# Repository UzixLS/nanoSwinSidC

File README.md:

## nanoSwinSidC

SID emulator on ATmega.

This is custom PCB variant of SwinSID Nano project.

See https://www.c64-wiki.com/wiki/SwinSID and http://www.tolaemon.com/nss/

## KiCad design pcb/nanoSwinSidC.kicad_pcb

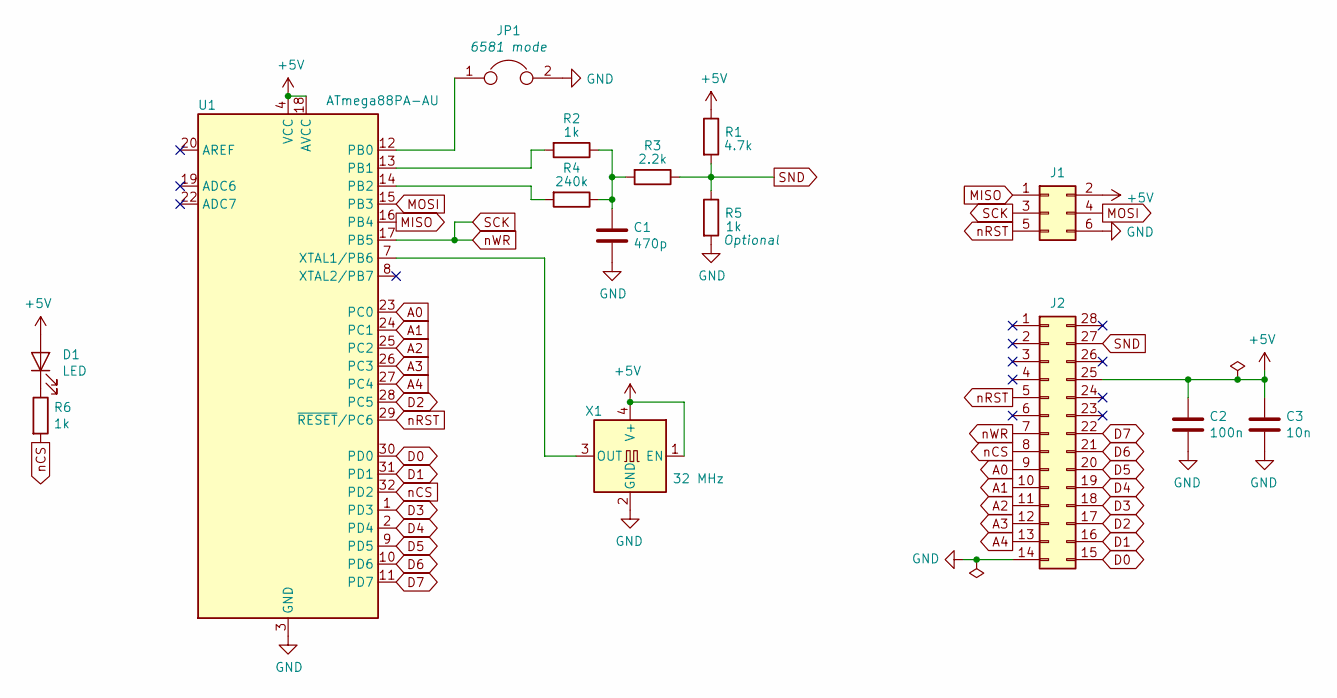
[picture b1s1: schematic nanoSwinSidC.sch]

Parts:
C1: 470p; C_0603_1608Metric_Pad1.05x0.95mm_HandSolder
C2: 100n; C_0603_1608Metric_Pad1.05x0.95mm_HandSolder
C3: 10n; C_0603_1608Metric_Pad1.05x0.95mm_HandSolder
D1: LED; LED_0805_2012Metric_Pad1.15x1.40mm_HandSolder
J1: Conn_02x03_Odd_Even; PinHeader_2x03_P2.54mm_Vertical
J2: Conn_02x14_Counter_Clockwise; DIP-28_W15.24mm
JP1: Jumper; PinHeader_1x02_P2.54mm_Horizontal
R1: 4.7k; R_0603_1608Metric_Pad1.05x0.95mm_HandSolder
R2, R5, R6: 1k; R_0603_1608Metric_Pad1.05x0.95mm_HandSolder
R3: 2.2k; R_0603_1608Metric_Pad1.05x0.95mm_HandSolder
R4: 240k; R_0603_1608Metric_Pad1.05x0.95mm_HandSolder
U1: ATmega88PA-AU; TQFP-32_7x7mm_P0.8mm
X1: 32 MHz; Oscillator_SMD_EuroQuartz_XO91-4Pin_7.0x5.0mm_HandSoldering

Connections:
+5V: C2.1, C3.1, D1.2 (A), J1.2, J2.25, R1.1, U1.4 (VCC), U1.6 (VCC), U1.18 (AVCC), X1.1 (EN), X1.4 (V+)
A0: J2.9, U1.23 (PC0)
A1: J2.10, U1.24 (PC1)
A2: J2.11, U1.25 (PC2)
A3: J2.12, U1.26 (PC3)
A4: J2.13, U1.27 (PC4)
D0: J2.15, U1.30 (PD0)
D1: J2.16, U1.31 (PD1)
D2: J2.17, U1.28 (PC5)
D3: J2.18, U1.1 (PD3)
D4: J2.19, U1.2 (PD4)
D5: J2.20, U1.9 (PD5)
D6: J2.21, U1.10 (PD6)
D7: J2.22, U1.11 (PD7)
GND: C1.2, C2.2, C3.2, J1.6, J2.14, JP1.2, R5.2, U1.3 (GND), U1.5 (GND), U1.21 (GND), X1.2 (GND)
MISO: J1.1, U1.16 (PB4)
MOSI: J1.4, U1.15 (PB3)
unnamed: C1.1, R2.1, R3.2, R4.1
unnamed: D1.1 (K), R6.1
unnamed: JP1.1, U1.12 (PB0)
unnamed: R2.2, U1.13 (PB1)
unnamed: R4.2, U1.14 (PB2)
unnamed: U1.7 (XTAL1/PB6), X1.3 (OUT)
SCK: J1.3, J2.7, U1.17 (PB5)
SND: J2.27, R1.2, R3.1, R5.1
nCS: J2.8, R6.2, U1.32 (PD2)
nRST: J1.5, J2.5, U1.29 (~RESET~/PC6)

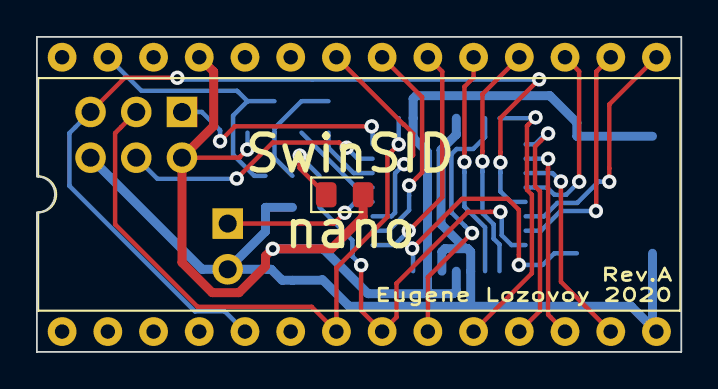
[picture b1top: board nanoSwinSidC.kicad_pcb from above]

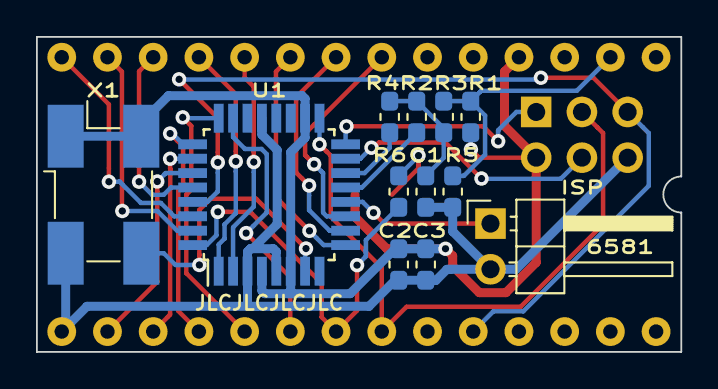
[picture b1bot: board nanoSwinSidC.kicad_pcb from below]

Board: 2 copper layers, 35.8 x 17.5 mm, 15 parts (12 on the bottom side), 27 nets.

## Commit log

2020-05-17 init
2020-05-18 improve pcb layout
2020-07-27 add derived files
2020-07-27 add firmware
2020-07-29 fix github language detector
2021-04-08 update 3d renders
2021-04-08 add photos
2022-06-19 add license
2026-06-17 remove raw=true from README links
